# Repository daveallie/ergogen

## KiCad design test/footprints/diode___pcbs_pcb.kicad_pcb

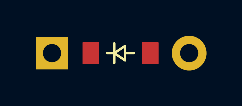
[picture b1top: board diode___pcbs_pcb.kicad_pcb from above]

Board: 2 copper layers, 3 parts (0 on the bottom side), 2 nets, no tracks yet.

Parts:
D1, D2, D3: ComboDiode

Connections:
from: D1.2, D2.2, D3.2
to: D1.1, D2.1, D3.1

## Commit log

2022-08-28 Allow side param in promicro footprint to flip text
2022-08-28 Add .idea to .gitignore
2022-08-28 Add optional through holes for diodes
2022-08-28 Allow all pins on slider to be defined
2022-08-28 Add PTS636 SK43 LFS button type
2022-08-28 Remove slider NPTH footprints from copper layers
2022-08-28 Add internalVia option to diode
2024-07-19 Allow diode SMD/THT footprints to be disabled
2024-07-19 Add internal vias option to diodes
2024-07-19 Add via in pad option for diodes
2024-07-19 More consistent formatting for promicro footprint + tests
2024-07-19 DRY up src/footprints/promicro.js
    My aim here is that this will make it easier to reuse the code for other
    MCUs.
2024-07-19 Remove 45 degree rotation on promicro pin 1
2024-07-19 Add support for selecting PCB side for promicro
2024-07-19 Add PTS636_SK43_LFS variant for button
2024-07-19 Allow allow slider nets to be referenced
